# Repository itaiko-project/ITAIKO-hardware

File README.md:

**ITAIKO** is an open-source, DIY drum controller for *Taiko no Tatsujin* and its simulators. 

Built for rhythm game enthusiasts who want to build an arcade-quality drum at home, or for those who want to update their older drum with a newer and better e-box, the **onigiri-con!**

This project is heavily inspired by, and builds upon the incredible groundwork laid by:
* [**ravinrabbid's DonCon2040**](https://github.com/ravinrabbid/DonCon2040) for the base firmware and console compatibility!
* [**kasashiki3's HIDtaiko**](https://github.com/kasasiki3/HIDtaiko) for the passive sensors cleanup cicuit!

---

## ✨ Features

* **Arcade-like accuracy:** The firmware has been modified with a simple but effective algorithm that provides near-perfect readings even on the cheapest sensors!
* **Low Latency:** The passive cleanup circuit only uses **two diodes** to improve the readablity of the sensors, and combined with the speed of the RP2040 provides super fast readings without any operational amplifiers and active electronics!
* [**Web Configurator:**](https://itaiko.com/) A web-usb based configurator that works on Chromium-based browsers and Firefox*, it supports auto updating, key remapping and includes a built-in drum tester inspired by [**the Zhong Taiko Controller Tester.**](https://tktest.taiko.ac/)
* **Multi-Platform Support:** It's compatible with PC, PS4**, Switch, Android, iOS and even PS3!
* **Fully Open Source:** From the drum, to the onigiri, you can easily 3D print, laser cut and build your own ITAIKO! **We provide the files for everything you'll ever need.**

>*On firefox you'll need to install a lightweight extension to enable WebUSB

>**On PS4 you'll need to provide your own Dualshock 4 Private keys to avoid the 8 minute timeout!
---

## 🎮 Compatibility

**ITAIKO** is designed to be plug-and-play across various platforms. Below is the current compatibility status:

| Platform | Status | Notes |
| :--- | :--- | :--- |
| **PC (Windows/Mac/Linux)** | 🟢 Native | Works instantly with osu!taiko, TJAPlayer3, Taiko Web, etc. Maps as a standard USB gamepad, keyboard or XInput device. |
| **Android / iOS** | 🟢 Native | Works via USB OTG adapter as a standard gamepad/keyboard! |
| **Nintendo Switch (Hori Switch mode)** | 🟢 Native | Spoofs the official HORI Taiko Drum controller. Plug into the dock and play. |
| **PlayStation 3** | ⚠️ Currently untested | Should work as a Dualshock 3. |
| **PlayStation 4 (Hori PS4 mode)** | 🟡 Requires Auth | To avoid restarting the e-box every 8 minutes, **you'll need to provide your own Dualshock 4 private keys** (You can drag-drop them in the web configurator!) |
| **PlayStation 5** | ⚠️ Currently untested | Should work on PS4 backward-compatible games. PS4 limitation still apply here. |

---

##  Hardware

To build your own ITAIKO, you will need a mix of 3D printed parts, basic electronics, and woodwork.

This section is a WIP and will change constantly untill we get the drum design finalized. 

> A full, detailed Bill of Materials (BOM) and assembly guide will be added soon.

---

## Getting Started

>WIP

---

## Credits & Acknowledgements

This project would not exist without the open-source rhythm gaming community. Massive thanks to:

**Kasashiki3**, which made non-amplified piezo readings  comparable to amplified boards!

**ravinrabbid** with his amazing firmware on which we built our upon.

**The Taiko home drumming community** for sharing precious data necessary for this project to come to life.

**Zhong and all the other drum makers** for making arcade accurate home drumming a reality.

---

## License

This project is licensed under the **Creative Commons Attribution-NonCommercial-ShareAlike 4.0 International License (CC BY-NC-SA 4.0)**.

To view a copy of this license, visit [https://creativecommons.org/licenses/by-nc-sa/4.0/](https://creativecommons.org/licenses/by-nc-sa/4.0/).

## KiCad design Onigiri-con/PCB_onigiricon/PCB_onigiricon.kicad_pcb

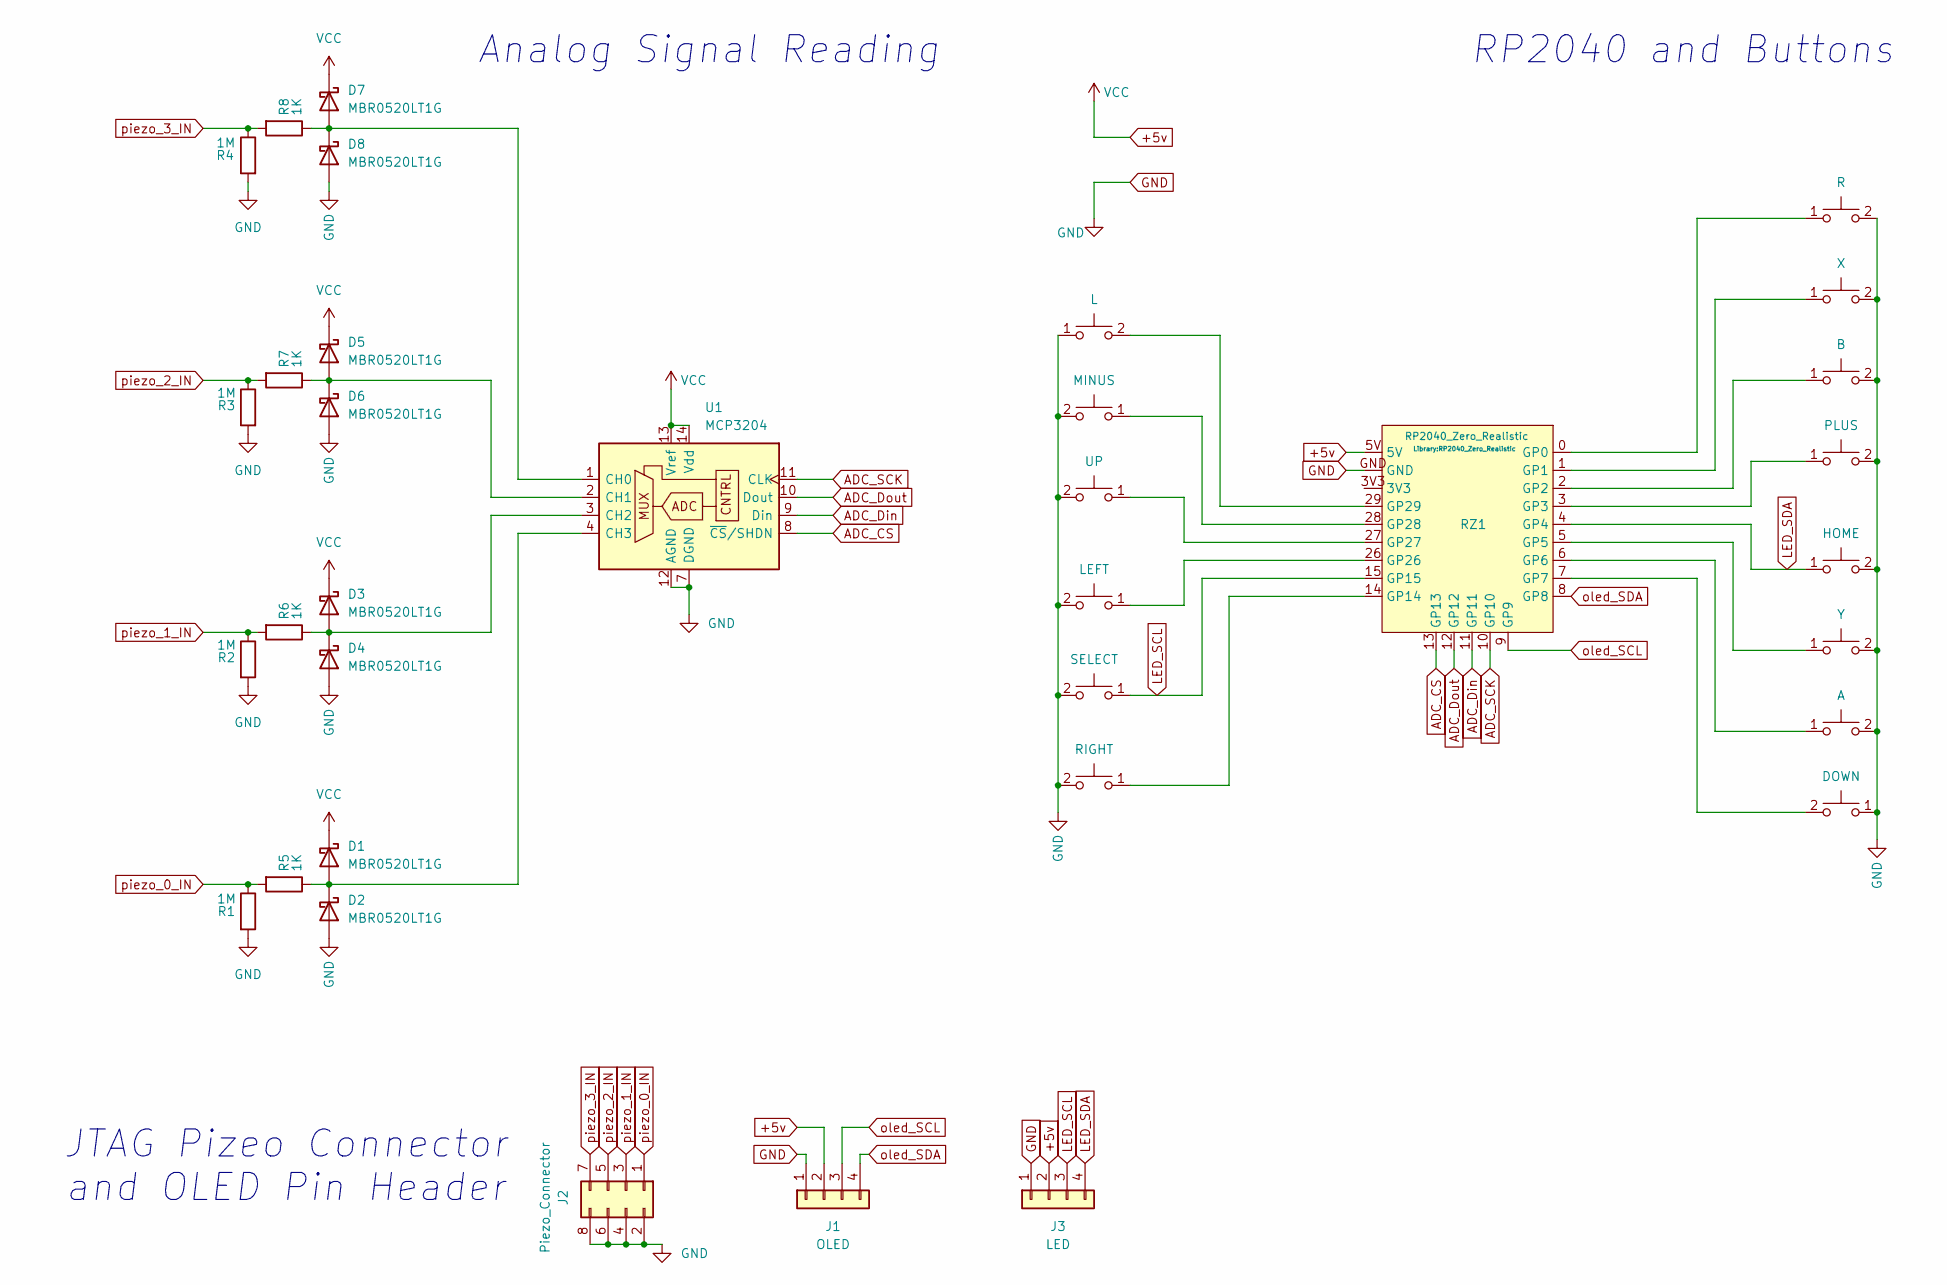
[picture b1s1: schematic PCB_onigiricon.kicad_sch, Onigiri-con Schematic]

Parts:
D1, D2, D3, D4, D5, D6, D7, D8: MBR0520LT1G; D_SOD-123
J1: OLED; PinSocket_1x04_P2.54mm_Vertical
J2: Piezo_Connector; IDC-Header_2x04_P2.54mm_Horizontal
J3: LED; PinSocket_1x04_P2.54mm_Vertical
R1, R2, R3, R4: 1M; R_0805_2012Metric
R5, R6, R7, R8: 1K; R_0805_2012Metric
RZ1: RP2040_Zero_Realistic
SW1: X; SW_SPST_CK_RS282G05A3
SW2: A; SW_SPST_CK_RS282G05A3
SW3: B; SW_SPST_CK_RS282G05A3
SW4: Y; SW_SPST_CK_RS282G05A3
SW5: PLUS; SW_SPST_CK_RS282G05A3
SW6: HOME; SW_SPST_CK_RS282G05A3
SW9: UP; SW_SPST_CK_RS282G05A3
SW10: LEFT; SW_SPST_CK_RS282G05A3
SW11: DOWN; SW_SPST_CK_RS282G05A3
SW12: RIGHT; SW_SPST_CK_RS282G05A3
SW13: MINUS; SW_SPST_CK_RS282G05A3
SW14: SELECT; SW_SPST_CK_RS282G05A3
SW15: R; SW_SPST_CK_RS282G05A3
SW16: L; SW_SPST_CK_RS282G05A3
U1: MCP3204; SOIC-14_3.9x8.7mm_P1.27mm

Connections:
+5v: D1.1 (K), D3.1 (K), D5.1 (K), D7.1 (K), J1.2, J3.2, RZ1.5V, U1.13 (Vref), U1.14 (Vdd)
ADC_CS: RZ1.13 (GP13), U1.8 (~CS/SHDN)
ADC_Din: RZ1.11 (GP11), U1.9 (Din)
ADC_Dout: RZ1.12 (GP12), U1.10 (Dout)
ADC_SCK: RZ1.10 (GP10), U1.11 (CLK)
GND: D2.2 (A), D4.2 (A), D6.2 (A), D8.2 (A), J1.1, J2.2, J2.4, J2.6, J2.8, J3.1, R1.2, R2.2, R3.2, R4.2, RZ1.GND, SW1.2 (D), SW2.2 (D), SW3.2 (D), SW4.2 (D), SW5.2 (D), SW6.2 (D), SW9.2 (D), SW10.2 (D), SW11.1 (C), SW12.2 (D), SW13.2 (D), SW14.2 (D), SW15.2 (D), SW16.1 (C), U1.7 (DGND), U1.12 (AGND)
LED_SCL: J3.3, RZ1.15 (GP15), SW14.1 (C)
LED_SDA: J3.4, RZ1.4 (GP4), SW6.1 (C)
unnamed: D1.2 (A), D2.1 (K), R5.1, U1.4 (CH3)
unnamed: D3.2 (A), D4.1 (K), R6.1, U1.3 (CH2)
unnamed: D5.2 (A), D6.1 (K), R7.1, U1.2 (CH1)
unnamed: D7.2 (A), D8.1 (K), R8.1, U1.1 (CH0)
unnamed: RZ1.0 (GP0), SW15.1 (C)
unnamed: RZ1.1 (GP1), SW1.1 (C)
unnamed: RZ1.2 (GP2), SW3.1 (C)
unnamed: RZ1.3 (GP3), SW5.1 (C)
unnamed: RZ1.5 (GP5), SW4.1 (C)
unnamed: RZ1.6 (GP6), SW2.1 (C)
unnamed: RZ1.7 (GP7), SW11.2 (D)
unnamed: RZ1.14 (GP14), SW12.1 (C)
unnamed: RZ1.26 (GP26), SW10.1 (C)
unnamed: RZ1.27 (GP27), SW9.1 (C)
unnamed: RZ1.28 (GP28), SW13.1 (C)
unnamed: RZ1.29 (GP29), SW16.2 (D)
oled_SCL: J1.3, RZ1.9 (GP9)
oled_SDA: J1.4, RZ1.8 (GP8)
piezo_0_IN: J2.1, R1.1, R5.2
piezo_1_IN: J2.3, R2.1, R6.2
piezo_2_IN: J2.5, R3.1, R7.2
piezo_3_IN: J2.7, R4.1, R8.2

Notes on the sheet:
RP2040 and Buttons
JTAG Pizeo Connector and OLED Pin Header
Analog Signal Reading

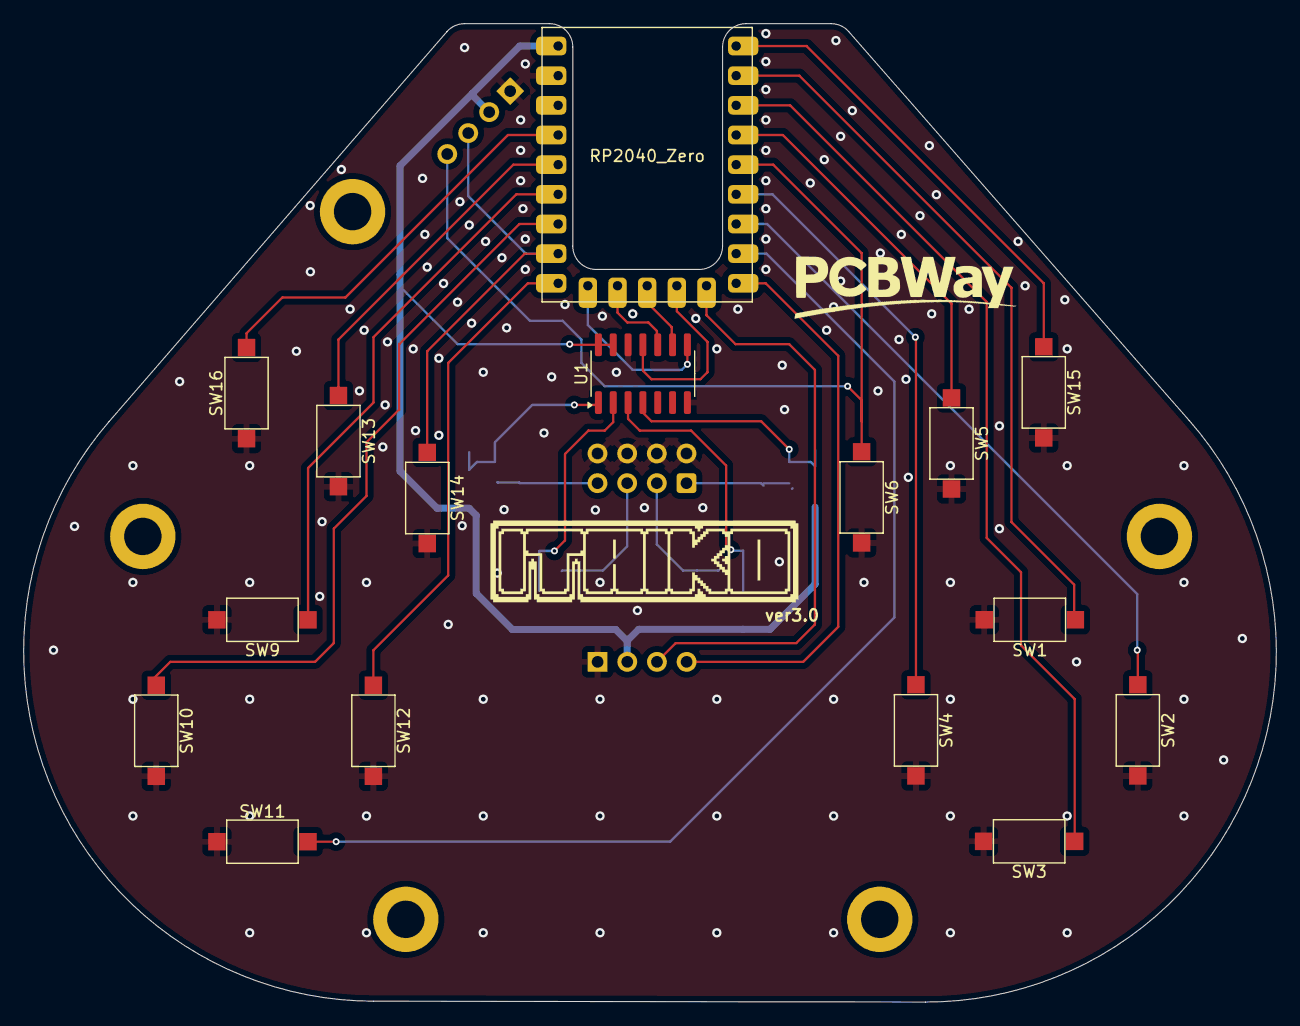
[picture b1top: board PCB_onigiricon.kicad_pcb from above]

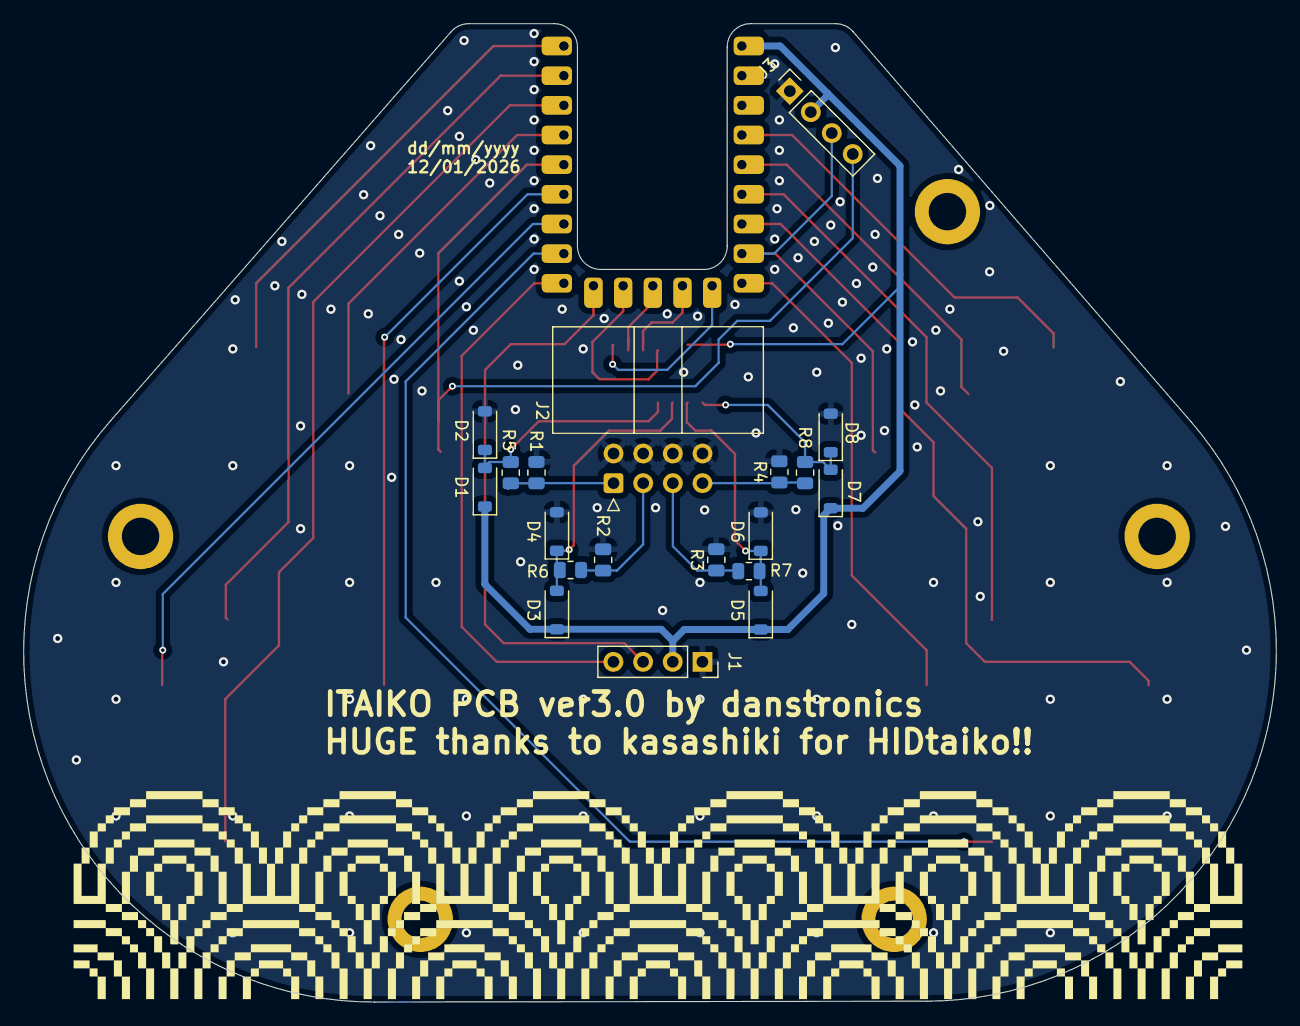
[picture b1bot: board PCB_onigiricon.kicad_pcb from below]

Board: 2 copper layers, 107.3 x 83.8 mm, 35 parts (19 on the bottom side), 30 nets.

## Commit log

2025-08-23 Removing everything non-ITAIKO
2026-04-07 Updated the repo with the latest PCB and STEP files.
    Slowly making the project fully open source!
2026-04-07 Fix banner in README.md
2026-04-16 Added upper Onigiri-con shell with smaller holes for tighter screw fit!
2026-04-17 Fixed raised + and - marks on the side buttons, updated the ready to print file with 2.9MM holes upper shell and updated + - buttons
